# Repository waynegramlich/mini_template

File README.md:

mini_template
=============

Mini-Shield Template for the Busino

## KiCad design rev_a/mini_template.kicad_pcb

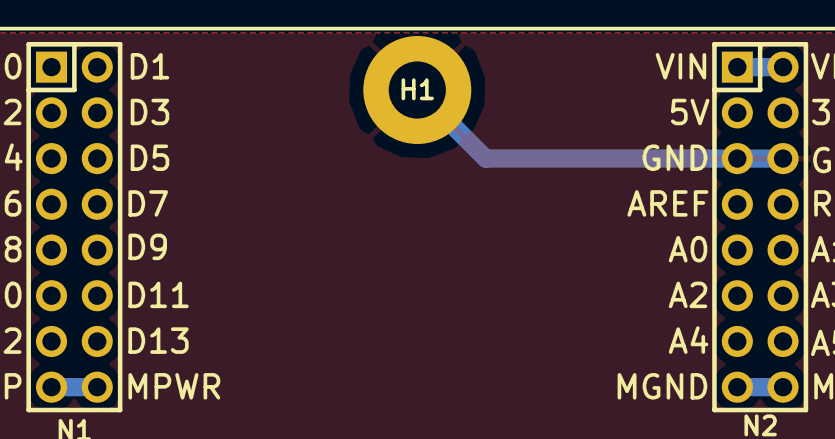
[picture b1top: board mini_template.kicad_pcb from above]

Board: 2 copper layers, 4 parts (0 on the bottom side), 4 nets.

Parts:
G1: OSHW_LOGO; OSHW_LOGO_400mil
H1: 3MM_HOLE; MountingHole_3mm
N1: MS_DATA_HEADER; Pin_Header_Straight_2x08
N2: MS_PWR_HEADER; Pin_Header_Straight_2x08

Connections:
/GND: H1.1, N2.5, N2.6
/MGND: N2.15, N2.16
/MPWR: N1.15, N1.16
/VIN: N2.1, N2.2

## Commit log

2014-06-25 Initial release of mini-shield template.
2014-06-25 Fixed open source hardware logo to have text.

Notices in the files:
rev_a/mini_template.kicad_pcb:
Copyright (c) 2014 by Wayne Gramlich
